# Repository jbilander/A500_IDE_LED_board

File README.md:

# A500_IDE_LED_board
Amiga 500 Floppy LED to Display IDE Activity too

Connect a fly-lead from IDE pin 39 /Active to J4 if U1 (74HCT2G14) is not populated, otherwise to J3

<br />

***

***

***
Connect a fly-lead from IDE pin 39 /Active
***

***

Video: <br />
https://drive.google.com/file/d/1Ml881xZoqoM8HT1IZ48qTFUnri6tXyhQ/view?usp=sharing

***

The individual pins in the pin-strip can be moved/pushed flush with the PCB holes before soldering. This is not necessary to do connection wise but it looks kind of nice when the bare pins are about the same length as the keyboard header on the Motherboard:

***

BOM Rev. A
---------
Position  | Name/Value   | Package | Notes
-|-|-|-|
U1 | 74HCT2G14 | TSOP-6 | Dual inverting Schmitt trigger
Q1 | BC857 or similar e.g. 2N3906 | SOT-23 | PNP general-purpose transistor
R1 | 10k | 1206 | Pull-up resistor
R2 | 4.7k | 1206 | Series resistor
C1 | 0.1uF = 100nF | 0805 | Decoupling capacitor
J1 | PinHeader_1x08_P2.54mm_Vertical | Single row 8pin | Pin 5 is not used and can be removed
J2 | PinSocket_1x08_P2.54mm_Vertical | Single row 8pin |
J3 | PinHeader_1x01_P2.54mm | Single pin | 
J4 | PinHeader_1x01_P2.54mm | Single pin |

***

[![CC BY-SA 4.0][cc-by-sa-shield]][cc-by-sa]

This work is licensed under a
[Creative Commons Attribution-ShareAlike 4.0 International License][cc-by-sa].

[![CC BY-SA 4.0][cc-by-sa-image]][cc-by-sa]

[cc-by-sa]: http://creativecommons.org/licenses/by-sa/4.0/
[cc-by-sa-image]: https://licensebuttons.net/l/by-sa/4.0/88x31.png
[cc-by-sa-shield]: https://img.shields.io/badge/License-CC%20BY--SA%204.0-lightgrey.svg

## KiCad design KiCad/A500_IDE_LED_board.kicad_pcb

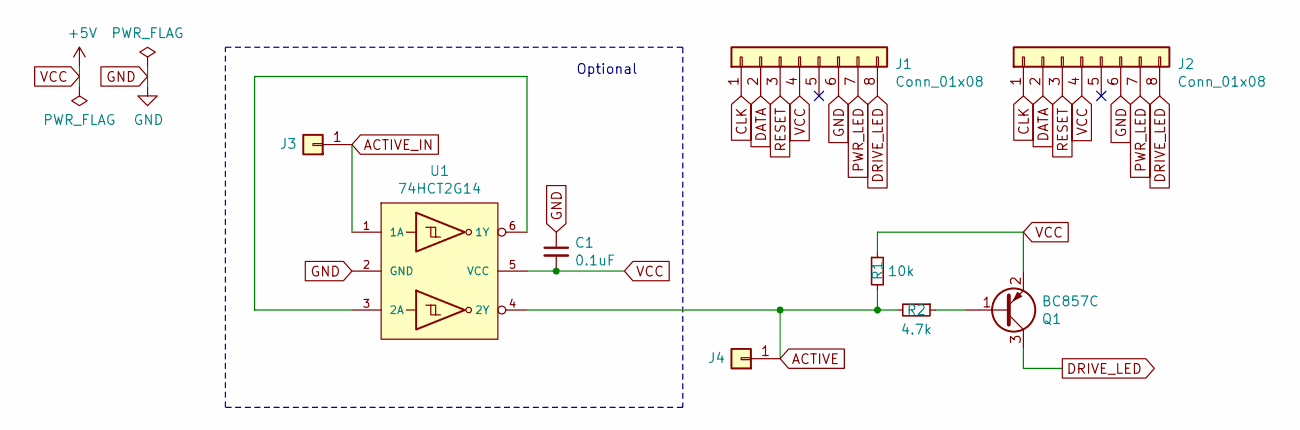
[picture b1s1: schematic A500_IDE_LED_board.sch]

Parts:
C1: 0.1uF; C_0805_2012Metric_Pad1.15x1.40mm_HandSolder
J1: Conn_01x08; PinHeader_1x08_P2.54mm_Vertical
J2: Conn_01x08; PinSocket_1x08_P2.54mm_Vertical
J3, J4: Conn_01x01; PinHeader_1x01_P2.54mm_Horizontal
Q1: BC857C; SOT-23
R1: 10k; R_1206_3216Metric_Pad1.42x1.75mm_HandSolder
R2: 4.7k; R_1206_3216Metric_Pad1.42x1.75mm_HandSolder
U1: 74HCT2G14; TSOP-6_1.65x3.05mm_P0.95mm

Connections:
ACTIVE: J4.1, R1.2, R2.2, U1.4 (2Y)
ACTIVE_IN: J3.1, U1.1 (1A)
CLK: J1.1, J2.1
DATA: J1.2, J2.2
DRIVE_LED: J1.8, J2.8, Q1.3 (C)
GND: C1.1, J1.6, J2.6, U1.2 (GND)
unnamed: Q1.1 (B), R2.1
unnamed: U1.3 (2A), U1.6 (1Y)
PWR_LED: J1.7, J2.7
RESET: J1.3, J2.3
VCC: C1.2, J1.4, J2.4, Q1.2 (E), R1.1, U1.5 (VCC)

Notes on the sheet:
Optional

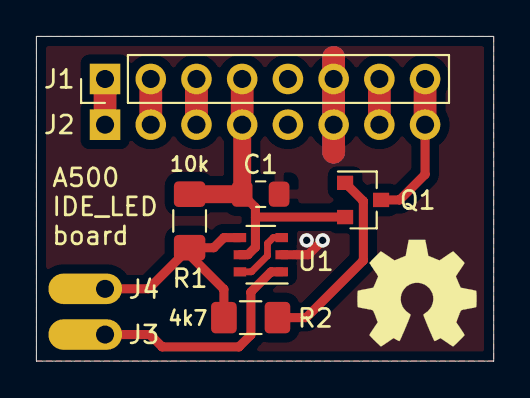
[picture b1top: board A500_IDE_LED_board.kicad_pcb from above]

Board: 2 copper layers, 25.4 x 18.0 mm, 9 parts (1 on the bottom side), 11 nets.

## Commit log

2022-03-09 added LICENSE
2022-03-10 added KiCad files
2022-03-10 added schematic pdf
2022-03-10 added output dir
2022-03-10 elongated J3-pad, and did some silkscreen fixes
2022-03-10 added Revision to silkscreen
2022-03-10 re-positioned J4 next to J3 and elongated pad
2022-03-10 added pics
2022-03-10 removed file
2022-04-27 added pic
2022-05-16 updated pic
